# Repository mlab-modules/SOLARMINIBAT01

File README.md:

# SOLARMINIBAT01

Battery module with [LTO cells](https://files.gwl.eu/inc/_doc/attach/StoItem/7015/GWL_LTO1865_Rechargeable.pdf). This module was primarily designed for use in autonomous outdoor devices powered by a solar cell. This is possible thanks to the use of LTO cells, which have a wide range of operating conditions and require minimal care. The device can therefore work in outdoor conditions all year round (tested in Central European conditions). 

### Features:
 * LTO batteries (4x LTO1865) cells
   * 1.3 Ah (per cell)
 * MPPT tracker for LTO batteries charging from solar cell
 * Battery gauge for battery charge state measurement
   * I2C interface
   * LED indication
 * Output switching voltage regulator
   *  Standard output voltage 3v3

## Schematics

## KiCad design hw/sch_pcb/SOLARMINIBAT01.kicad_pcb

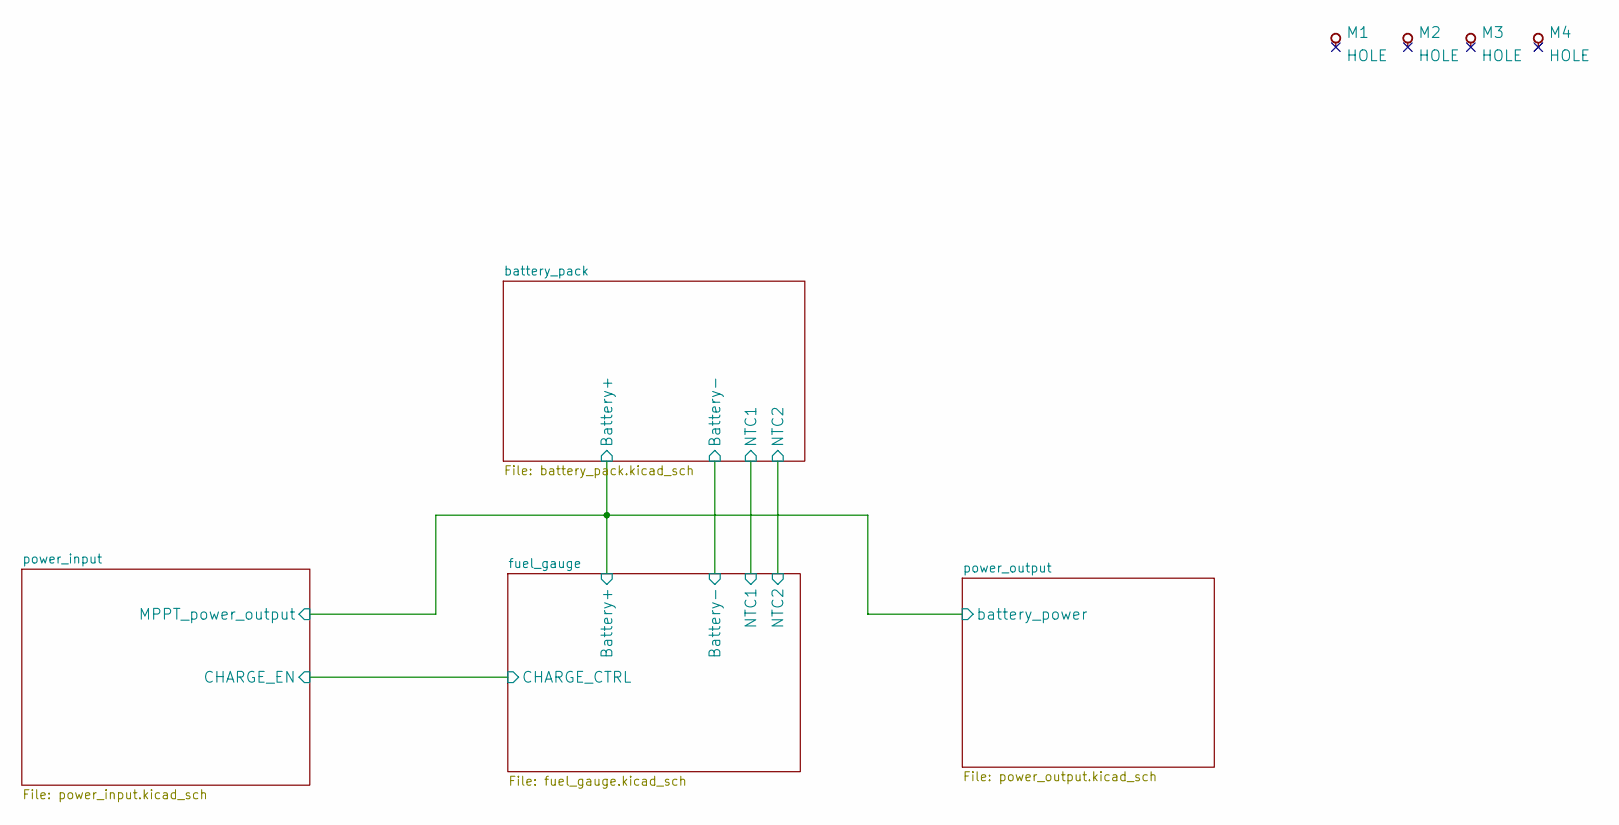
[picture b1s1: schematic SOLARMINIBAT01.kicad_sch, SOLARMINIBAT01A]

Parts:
M1, M2, M3, M4: HOLE; MountingHole_3mm

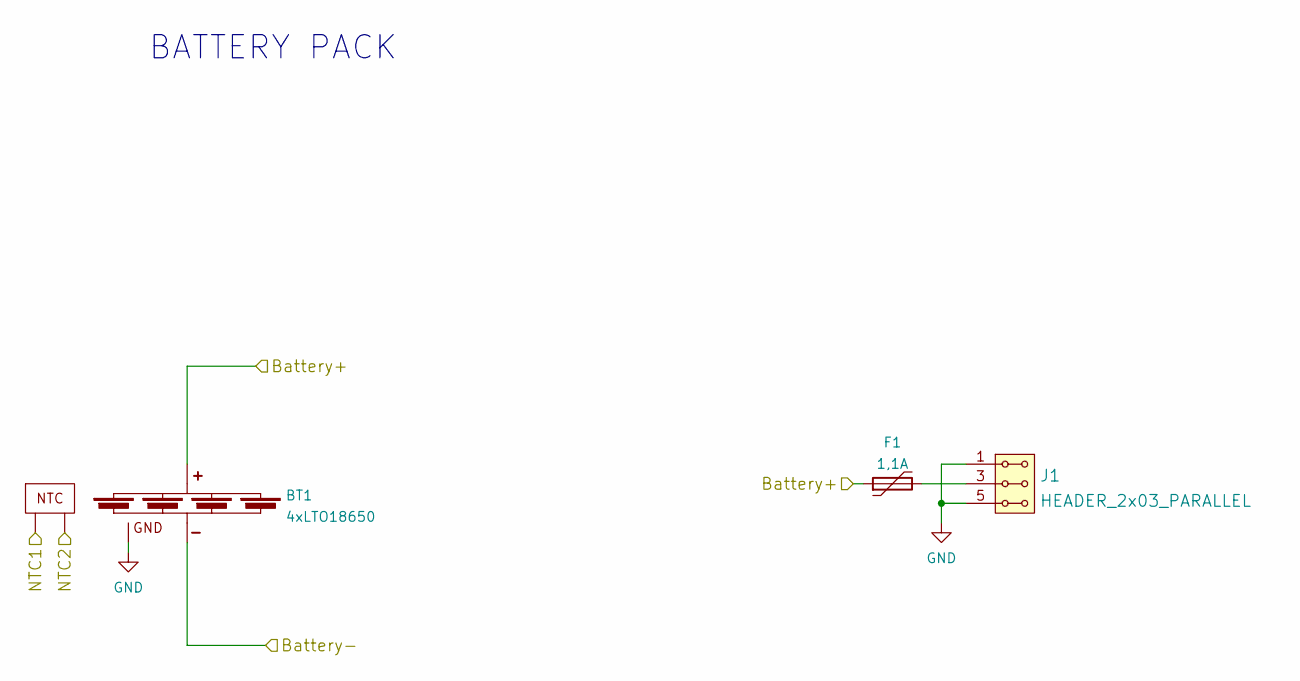
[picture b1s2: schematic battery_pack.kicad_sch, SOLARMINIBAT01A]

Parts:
BT1: 4xLTO18650; 4XLTO1865V01A
F1: 1,1A; Fuse_1812_4532Metric_Pad1.30x3.40mm_HandSolder
J1: HEADER_2x03_PARALLEL; Straight_2x03

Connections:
/battery_pack/Battery+: BT1.1 (+), F1.1; also elsewhere on the board
/battery_pack/Battery-: BT1.2 (-); also elsewhere on the board
/battery_pack/NTC1: BT1.5; also elsewhere on the board
/battery_pack/NTC2: BT1.6; also elsewhere on the board
GND: BT1.3 (GND), J1.1, J1.2, J1.5, J1.6; also elsewhere on the board
unnamed: F1.2, J1.3, J1.4

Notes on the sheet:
BATTERY PACK

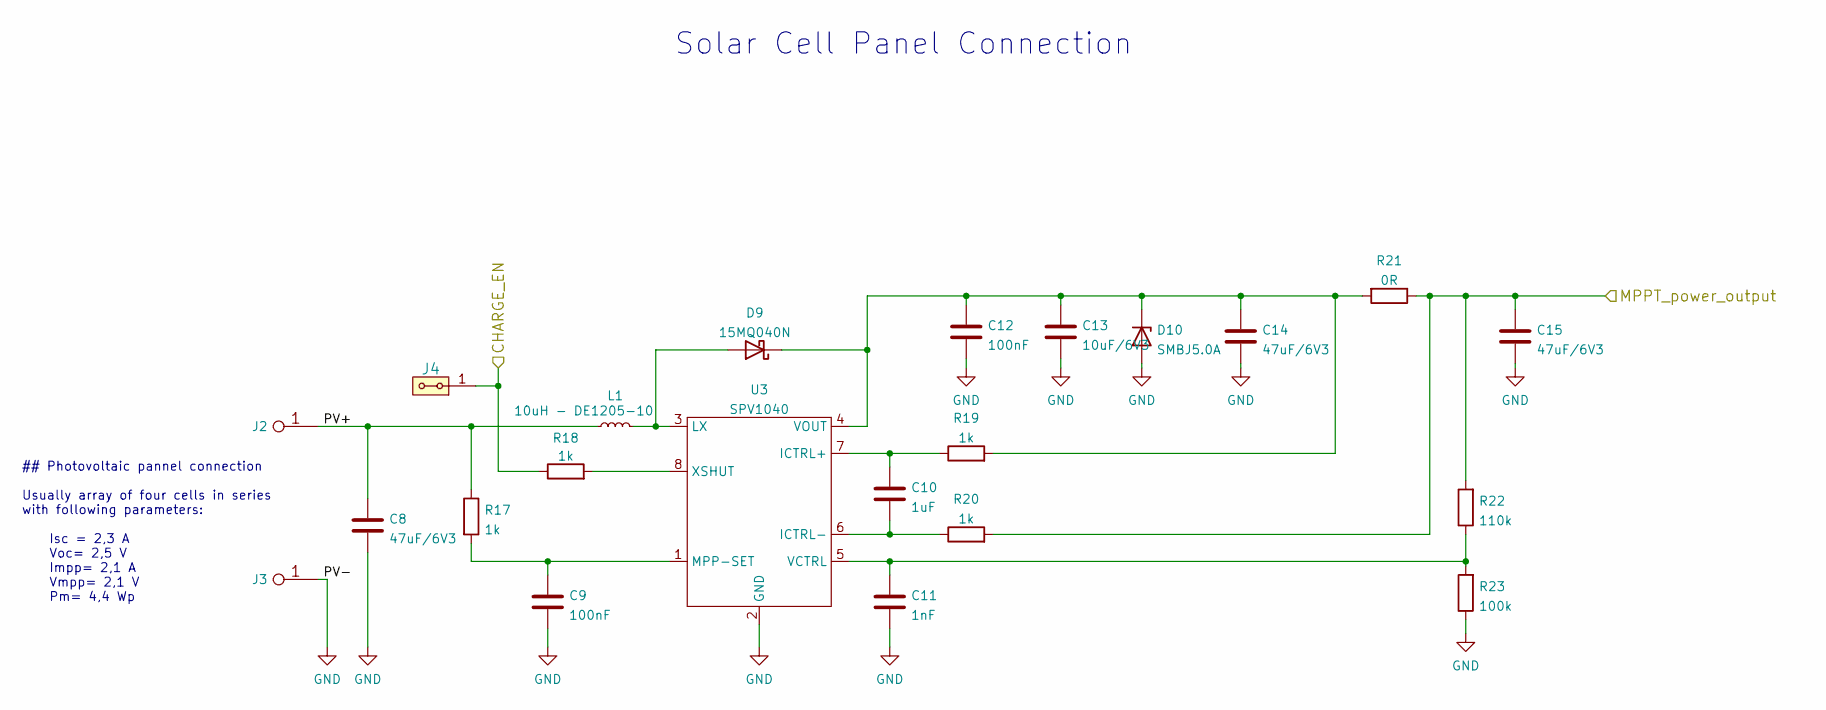
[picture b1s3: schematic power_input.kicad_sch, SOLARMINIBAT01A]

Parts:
C8, C14, C15: 47uF/6V3; C_0805_2012Metric
C9, C12: 100nF; C_0805_2012Metric
C10: 1uF; C_0805_2012Metric
C11: 1nF; C_0805_2012Metric
C13: 10uF/6V3; C_0805_2012Metric
D9: 15MQ040N; D_SMA
D10: SMBJ5.0A; D_SMA
J2: WAGO 256 ORANGE; WAGO256
J3: WAGO 256 BLUE; WAGO256
J4: HEADER_2x01_PARALLEL; Straight_2x01
L1: 10uH - DE1205-10; DE1205-10
R17, R18, R19, R20: 1k; R_0805_2012Metric
R21: 0R; R_1206_3216Metric
R22: 110k; R_0805_2012Metric
R23: 100k; R_0805_2012Metric
U3: SPV1040; TSSOP-8_4.4x3mm_P0.65mm

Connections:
/battery_pack/Battery+: C15.1, R20.2, R21.1, R22.2; also elsewhere on the board
/fuel_gauge/CHARGE_CTRL: J4.1, J4.2, R18.1; also elsewhere on the board
/power_input/PV+: C8.1, J2.1, L1.1, R17.1
GND: C8.2, C9.2, C11.2, C12.2, C13.2, C14.2, C15.2, D10.2 (A), J3.1, R23.1, U3.2 (GND); also elsewhere on the board
unnamed: C9.1, R17.2, U3.1 (MPP-SET)
unnamed: C10.1, R19.1, U3.7 (ICTRL+)
unnamed: C10.2, R20.1, U3.6 (ICTRL-)
unnamed: C11.1, R22.1, R23.2, U3.5 (VCTRL)
unnamed: C12.1, C13.1, C14.1, D9.1 (K), D10.1 (K), R19.2, R21.2, U3.4 (VOUT)
unnamed: D9.2 (A), L1.2, U3.3 (LX)
unnamed: R18.2, U3.8 (XSHUT)

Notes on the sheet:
## Photovoltaic pannel connection Usually array of four cells in series with following parameters: Isc = 2,3 A Voc= 2,5 V Impp= 2,1 A Vmpp= 2,1 V Pm= 4,4 Wp
Solar Cell Panel Connection

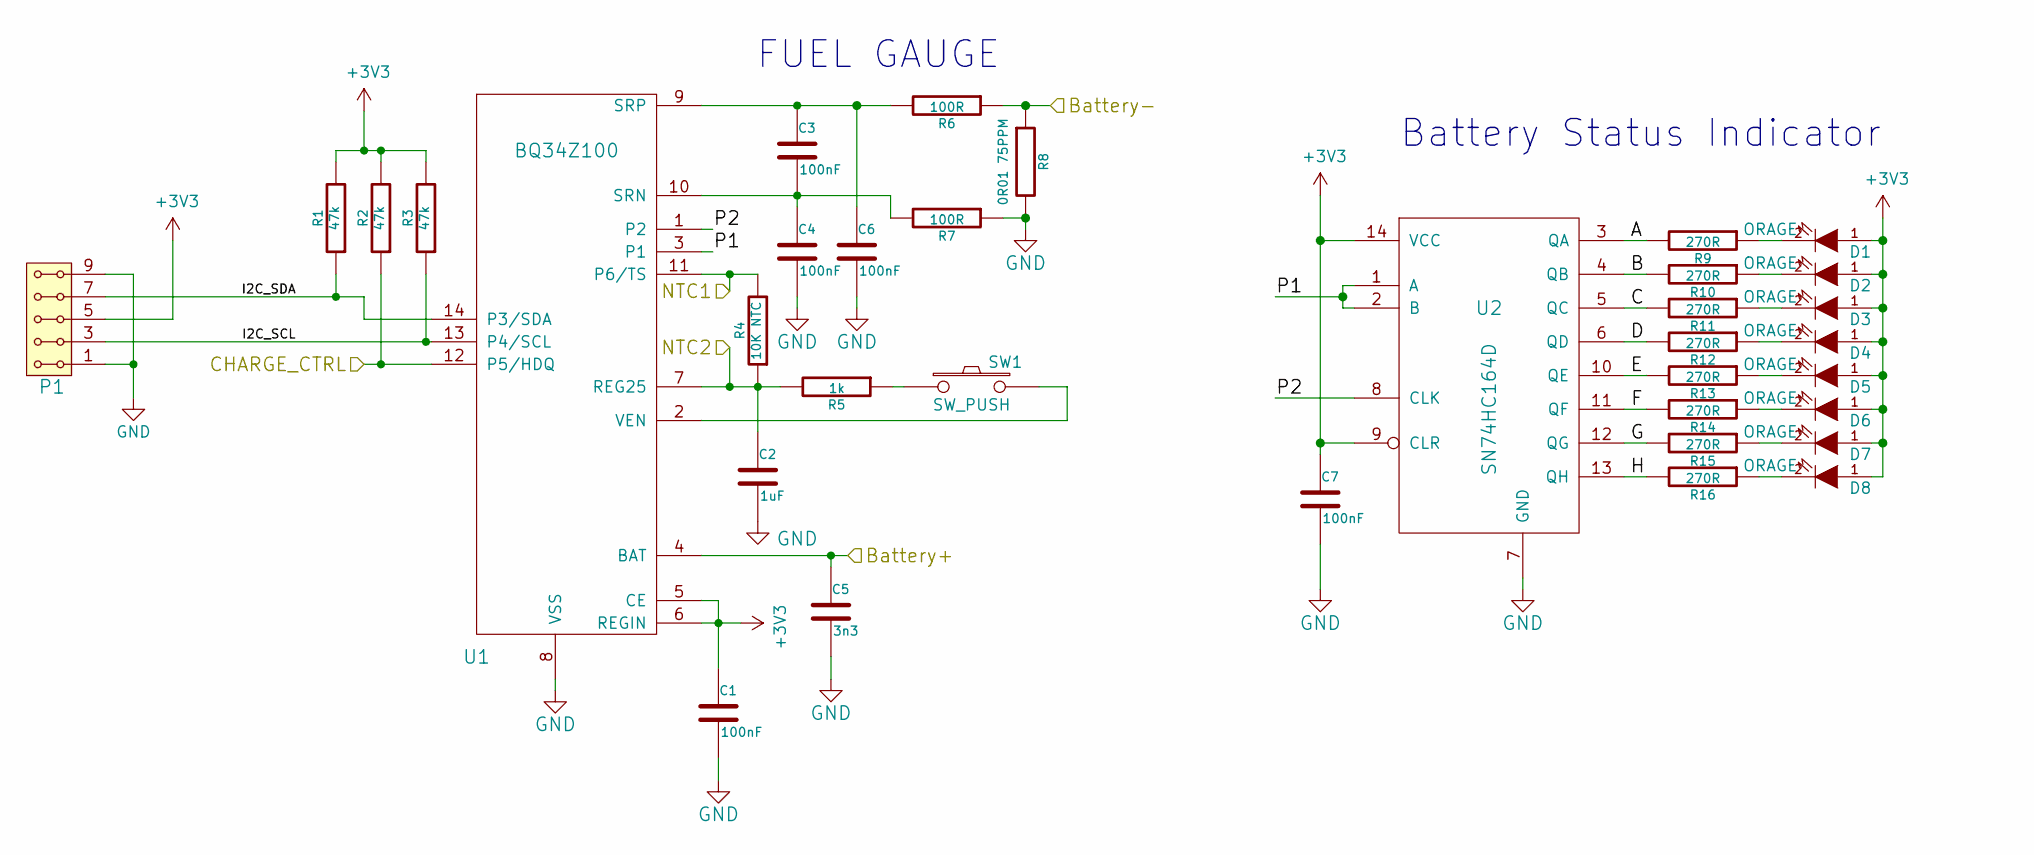
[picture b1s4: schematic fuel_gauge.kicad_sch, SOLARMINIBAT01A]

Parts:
C1, C3, C4, C6, C7: 100nF; C_0805_2012Metric
C2: 1uF; C_0805_2012Metric
C5: 3n3; C_0805_2012Metric
D1, D2, D3, D4, D5, D6, D7, D8: ORAGE; LED_1206
P1: HEADER_2x05_PARALLEL; Straight_2x05
R1, R2, R3: 47k; R_0805_2012Metric
R4: 10K NTC; R_0805_2012Metric_Pad1.20x1.40mm_HandSolder
R5: 1k; R_0805_2012Metric
R6, R7: 100R; R_0805_2012Metric
R8: 0R01 75PPM; R_2512_6332Metric_Pad1.40x3.35mm_HandSolder
R9, R10, R11, R12, R13, R14, R15, R16: 270R; R_0805_2012Metric
SW1: SW_PUSH; SW_PUSH_SMALL
U1: BQ34Z100; TSSOP-14_4.4x5mm_Pitch0.65mm
U2: SN74HC164D; SO-14_3.9x8.65mm_P1.27mm

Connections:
+3V3: C1.1, C7.1, D1.1 (A), D2.1 (A), D3.1 (A), D4.1 (A), D5.1 (A), D6.1 (A), D7.1 (A), D8.1 (A), P1.5, P1.6, R1.2, R2.2, R3.2, U1.5 (CE), U1.6 (REGIN), U2.9 (CLR), U2.14 (VCC); also elsewhere on the board
/battery_pack/Battery+: C5.1, U1.4 (BAT); also elsewhere on the board
/battery_pack/Battery-: R6.1, R8.1; also elsewhere on the board
/battery_pack/NTC1: R4.2, U1.11 (P6/TS); also elsewhere on the board
/battery_pack/NTC2: C2.1, R4.1, R5.2, U1.7 (REG25); also elsewhere on the board
/fuel_gauge/A: R9.2, U2.3 (QA)
/fuel_gauge/B: R10.2, U2.4 (QB)
/fuel_gauge/C: R11.2, U2.5 (QC)
/fuel_gauge/CHARGE_CTRL: R2.1, U1.12 (P5/HDQ); also elsewhere on the board
/fuel_gauge/D: R12.2, U2.6 (QD)
/fuel_gauge/E: R13.2, U2.10 (QE)
/fuel_gauge/F: R14.2, U2.11 (QF)
/fuel_gauge/G: R15.2, U2.12 (QG)
/fuel_gauge/H: R16.2, U2.13 (QH)
/fuel_gauge/I2C_SCL: P1.3, P1.4, R3.1, U1.13 (P4/SCL)
/fuel_gauge/I2C_SDA: P1.7, P1.8, R1.1, U1.14 (P3/SDA)
/fuel_gauge/P1: U1.3 (P1), U2.1 (A), U2.2 (B)
/fuel_gauge/P2: U1.1 (P2), U2.8 (CLK)
GND: C1.2, C2.2, C4.2, C5.2, C6.2, C7.2, P1.1, P1.2, P1.9, P1.10, R7.1, R8.2, U1.8 (VSS), U2.7 (GND); also elsewhere on the board
unnamed: C3.1, C6.1, R6.2, U1.9 (SRP)
unnamed: C3.2, C4.1, R7.2, U1.10 (SRN)
unnamed: D1.2 (K), R9.1
unnamed: D2.2 (K), R10.1
unnamed: D3.2 (K), R11.1
unnamed: D4.2 (K), R12.1
unnamed: D5.2 (K), R13.1
unnamed: D6.2 (K), R14.1
unnamed: D7.2 (K), R15.1
unnamed: D8.2 (K), R16.1
unnamed: R5.1, SW1.1
unnamed: SW1.2, U1.2 (VEN)

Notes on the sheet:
Battery Status Indicator
FUEL GAUGE

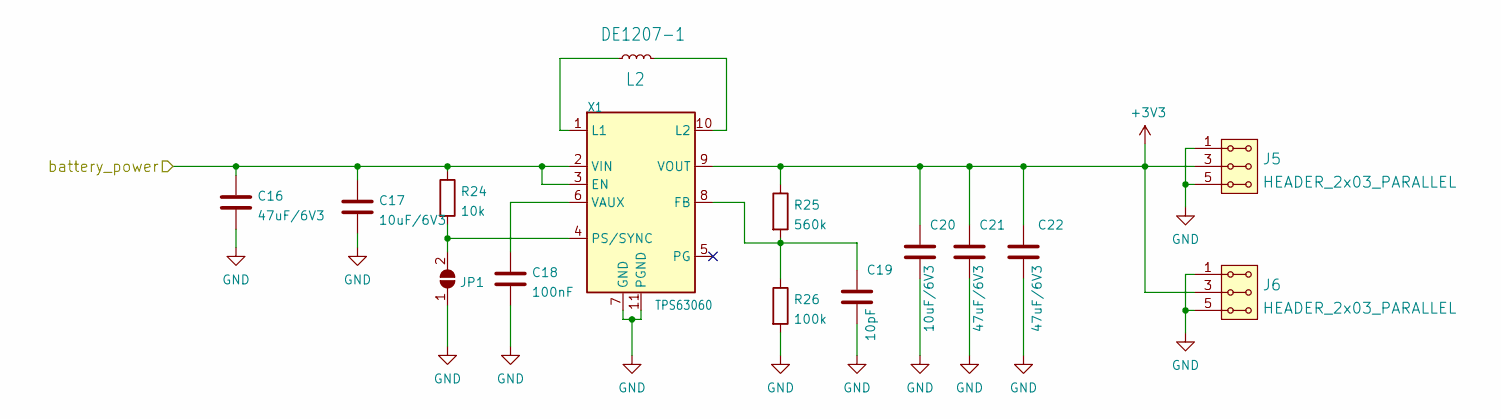
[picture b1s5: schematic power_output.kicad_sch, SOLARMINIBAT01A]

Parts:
C16, C21, C22: 47uF/6V3; C_0805_2012Metric
C17, C20: 10uF/6V3; C_0805_2012Metric
C18: 100nF; C_0805_2012Metric
C19: 10pF; C_0805_2012Metric
J5, J6: HEADER_2x03_PARALLEL; Straight_2x03
JP1: SolderJumper_2_Open; SolderJumper-2_P1.3mm_Open_RoundedPad1.0x1.5mm
L2: DE1207-1; DE1205-10
R24: 10k; R_0805_2012Metric
R25: 560k; R_0805_2012Metric
R26: 100k; R_0805_2012Metric
X1: TPS63060; Texas_S-PWSON-N10_ThermalVias

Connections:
+3V3: C20.1, C21.1, C22.1, J5.3, J5.4, J6.3, J6.4, R25.1, X1.9 (VOUT); also elsewhere on the board
/battery_pack/Battery+: C16.1, C17.1, R24.1, X1.2 (VIN), X1.3 (EN); also elsewhere on the board
GND: C16.2, C17.2, C18.2, C19.2, C20.2, C21.2, C22.2, J5.1, J5.2, J5.5, J5.6, J6.1, J6.2, J6.5, J6.6, JP1.1 (A), R26.2, X1.7 (GND), X1.11 (PGND); also elsewhere on the board
unnamed: C18.1, X1.6 (VAUX)
unnamed: C19.1, R25.2, R26.1, X1.8 (FB)
unnamed: JP1.2 (B), R24.2, X1.4 (PS/SYNC)
unnamed: L2.1, X1.1 (L1)
unnamed: L2.2, X1.10 (L2)

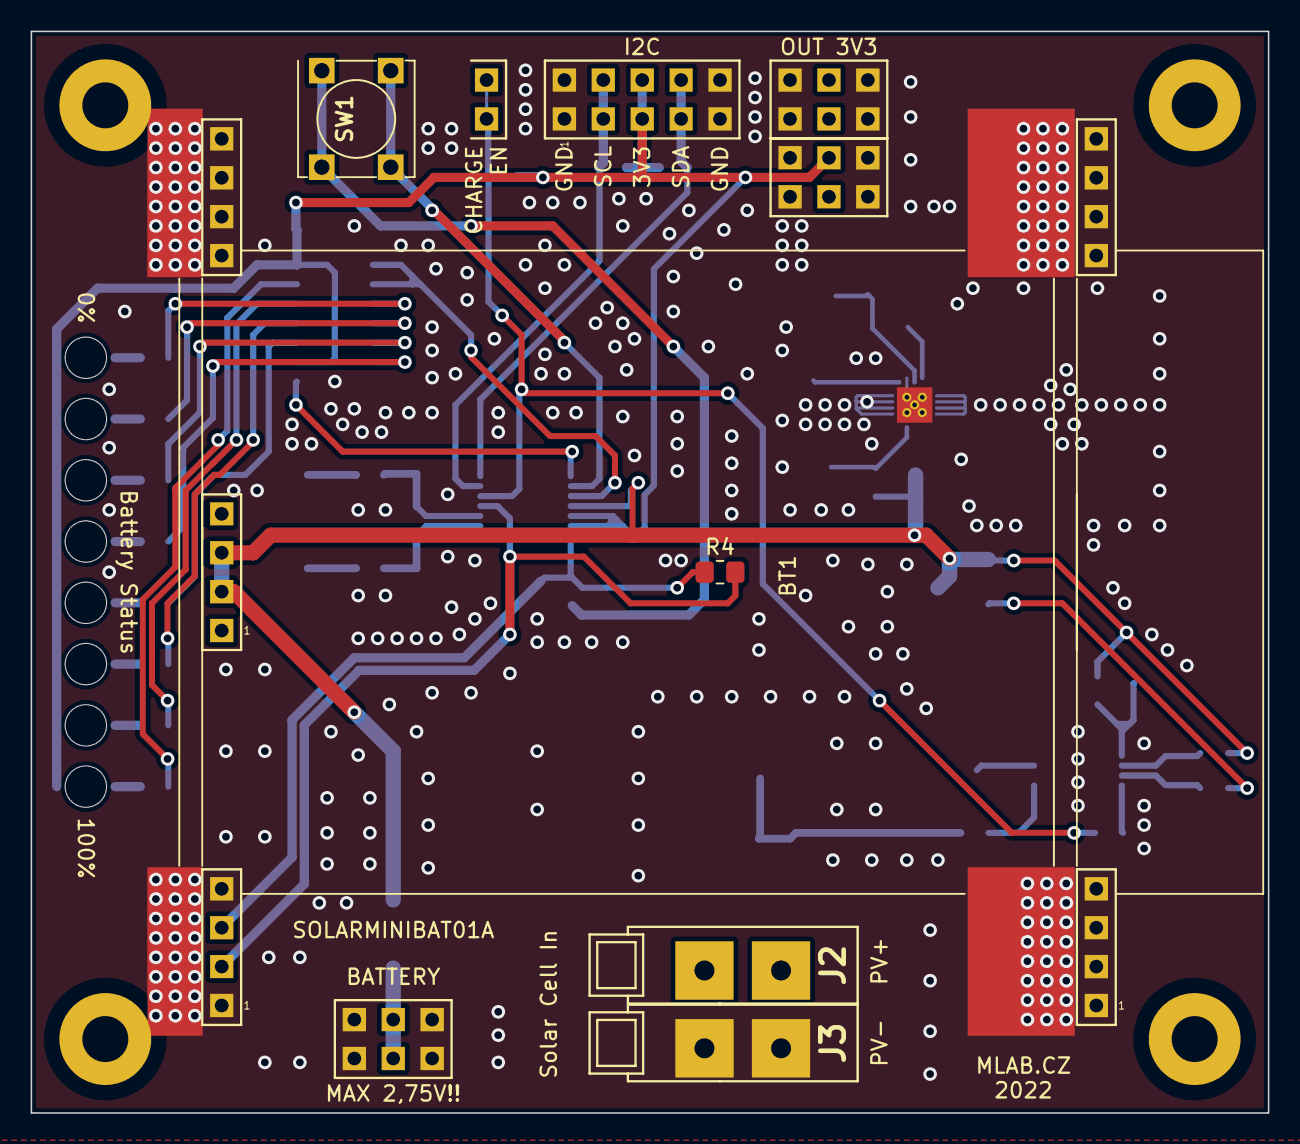
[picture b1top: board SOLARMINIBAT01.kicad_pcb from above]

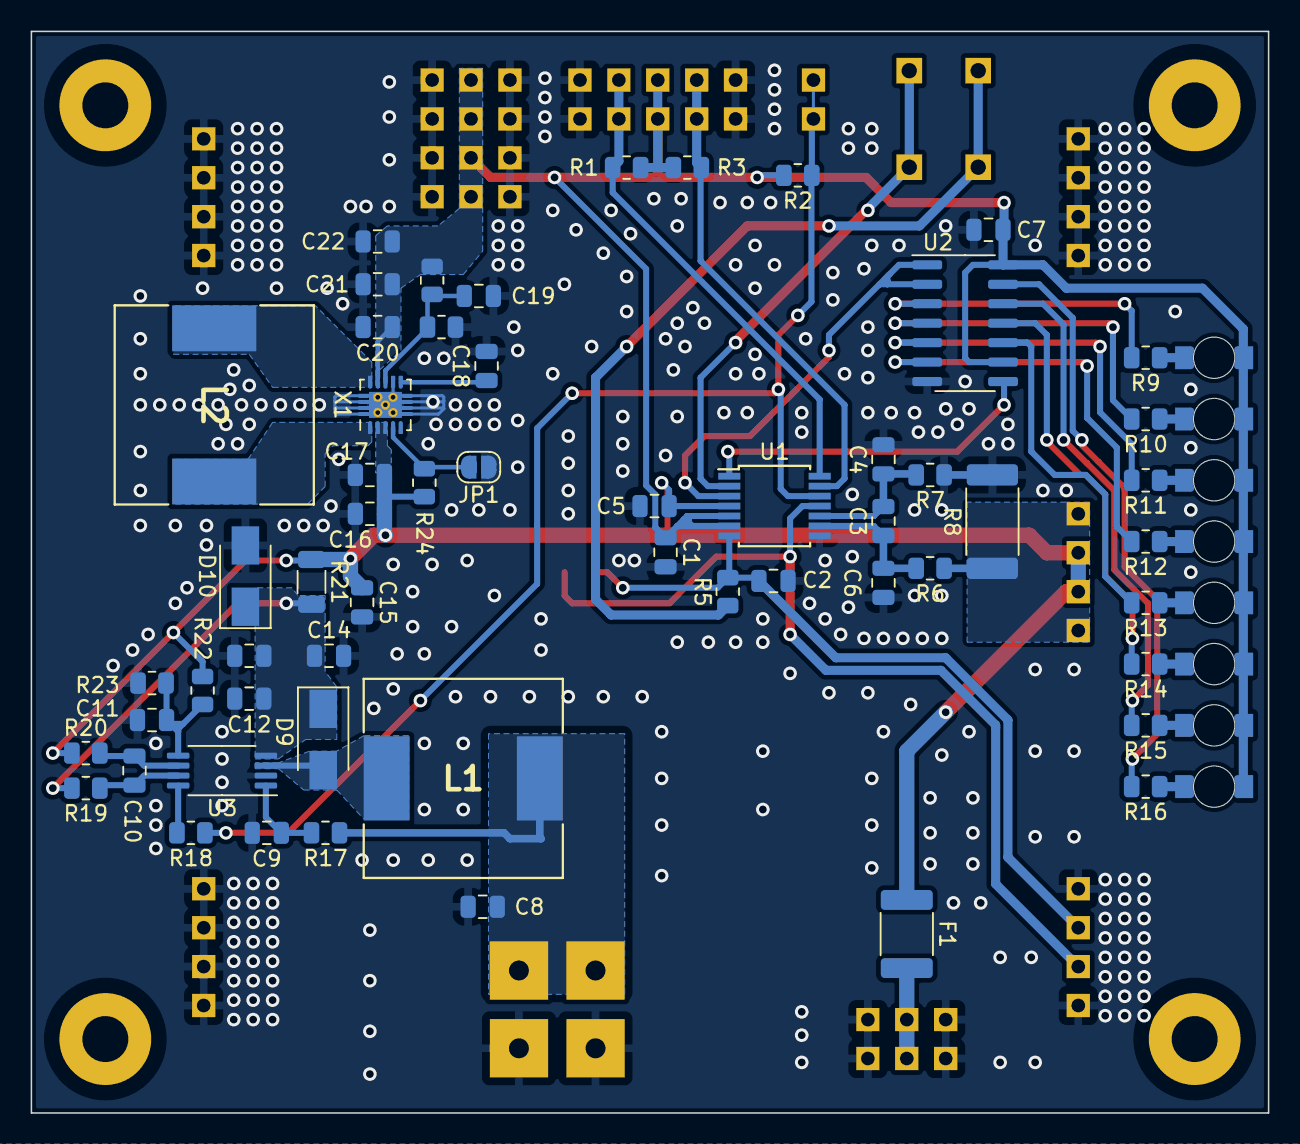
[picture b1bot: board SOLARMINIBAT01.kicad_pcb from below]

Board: 2 copper layers, 80.8 x 70.6 mm, 79 parts (65 on the bottom side), 45 nets.

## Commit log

2022-04-06 automated commit; add github actions
2022-07-20 start design of new module
2022-07-20 Prejmenovani projektu Kicad
2022-07-20 Pridano schema menice ze solarniho clanku
2022-07-20 Adding input switching regulator.
2022-07-20 cleanup unused file.
2022-07-20 finish gauge schematics design.
2022-07-20 Edit schema
2022-07-21 Update schematics: Adding datasheet Update title blocks Update pull-up value for CHARGE_CTRL signal.
2022-07-25 Edit PCB
2022-08-10 Edit kicad_outputs.yml
2022-08-10 Update actions products
2022-08-15 Edit UST ID
2022-08-16 Editing FAB layer
2022-10-16 Photos of module.
2023-01-11 Add a link to diode datasheet.
2023-01-15 battery printed holder - source
2023-01-15 gcode
2023-04-13 cleanup.
2023-05-13 Delete SOLARMINIBAT01A.pdf
    Obsolete file
2023-05-28 Update metadata files
2023-06-14 Update workflow files
2023-07-05 automated commit; rename source files to new naming convence
2023-07-25 battery contacts cover
2023-09-16 Update status
2024-09-21 Add datasheet to the used LTO cells. Improve documentation, update KiCAD project.
2024-09-29 Improved documentation and schematics. Output divider values changed to better fit maximum cell voltage.
